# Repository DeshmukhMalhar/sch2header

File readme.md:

# Generate pin definition header file form KiCAD schematic #
The firmware of microcontroller used has to have the correct pins connected to the peripherals in it. This project tries to automatically generate a pindefinitions.h file. This file can be included to your firmware project directly. The net names assigned to the pins in the schematic are #define*d* with actual pin names in the symbol library. So you can assign sensible names to pins and automagically use those in you code.
Generally, this is done manually, which might introduce errors.
Thus, this effort of automating it.

## SCOPE: ##
- Try to generate pindefs.h completely automatically
- try to integrate it in CI, i.e. when pushed, trigger build to generate pindefs.h
- maybe, in KiCAD 6, this can be run on exit of the sch editor, or on run of netlist generator.
- Currently in KiCAD 5.1.x , if possible I will try to make it a BOM script.(it might be possible more than I think)

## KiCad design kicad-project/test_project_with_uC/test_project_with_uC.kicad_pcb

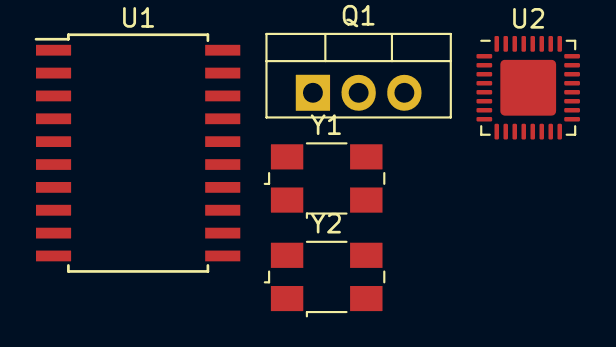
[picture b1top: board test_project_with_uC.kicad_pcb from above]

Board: 2 copper layers, 5 parts (0 on the bottom side), 12 nets, no tracks yet.

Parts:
Q1: IRF540N; TO-220-3_Vertical
U1: ATtiny2313-20SU; SOIC-20W_7.5x12.8mm_P1.27mm
U2: ATmega328-MU; QFN-32-1EP_5x5mm_P0.5mm_EP3.1x3.1mm
Y1: 12M; Crystal_SMD_0603-4Pin_6.0x3.5mm
Y2: 16M; Crystal_SMD_0603-4Pin_6.0x3.5mm

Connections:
+3V3: U1.20, U2.4, U2.6, U2.18
/MISO: U1.18, U2.16
/MOSFET_GATE: Q1.1, U2.12
/MOSI: U1.17, U2.15
/RXD: U1.2, U2.30
/SCK: U1.19, U2.17
/TXD: U1.3, U2.31
GND: Q1.3, U1.10, U2.3, U2.5, U2.21, U2.33
unnamed: U1.4, Y1.2
unnamed: U1.5, Y1.1
unnamed: U2.7, Y2.2
unnamed: U2.8, Y2.1

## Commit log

2019-05-20 added kicad project as a submodule
2019-05-20 file for test of read sch file nad netlist
2019-05-20 started extracting data from netlist
2019-05-20 read part values
2019-05-21 ignore .pdf files
2019-05-21 added a kaanban board
2019-05-27 Trying out kinparse module
2019-05-27 Ignored vscode files
2019-05-27 trying to extract footprint mapping section
2019-05-27 Vscode update
2019-05-27 update sub
2019-05-27 stopped ignoring .xml files
2019-05-27 sample test project for further testing
2019-05-27 remove submodule
2019-05-27 scripts for parsing and generating xml netlist
2019-05-29 ignored kicad temp and user conmments
2019-05-29 tables before intermidiate table are generated
2019-05-29 changed microcontroller symbol
2019-05-29 rearrange files
2019-05-29 add another microcontroller, for real world scene
2019-05-29 tried kinparse, unable to get complete part
2019-05-29 Started generating intermidiate table
2019-05-29 pin table and net table success, but out of order
2019-08-07 change from .getelement() to list()
2019-08-11 Modified the method of cpu_pin_table generation
2019-08-13 add more parts to the sch for testing
2019-08-13 correct pin map can be generated now
2019-09-21 update gitignore
2019-09-21 header generation successful
2019-09-21 kicad save
2019-11-14 testing with different order of input list
2019-12-04 testing with launch from kicad BOm generator
2019-12-06 changed KiCAD files to include XTAL for testing
2019-12-06 The final File that works, need restructured repo
2019-12-06 A information text about autogenerated headers
2019-12-06 ignore .pyc and testing autogen headers
